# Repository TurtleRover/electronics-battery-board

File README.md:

<p align="center">
  
</p>
<h1 align="center">Electronics: Battery board</h1>
<h4 align="center">This is battery board designed for Turtle rover.</h4>  

<p align="center">

</p>
<p align="center">
  <a href="http://turtlerover.com" alt="Website">Website</a> |
  <a href="https://www.facebook.com/TurtleRover/" alt="Facebook">Facebook</a> |
  <a href="https://www.youtube.com/channel/UCxukvEct3wP0S5FACa3uelA" alt="YouTube">YouTube</a>
</p>

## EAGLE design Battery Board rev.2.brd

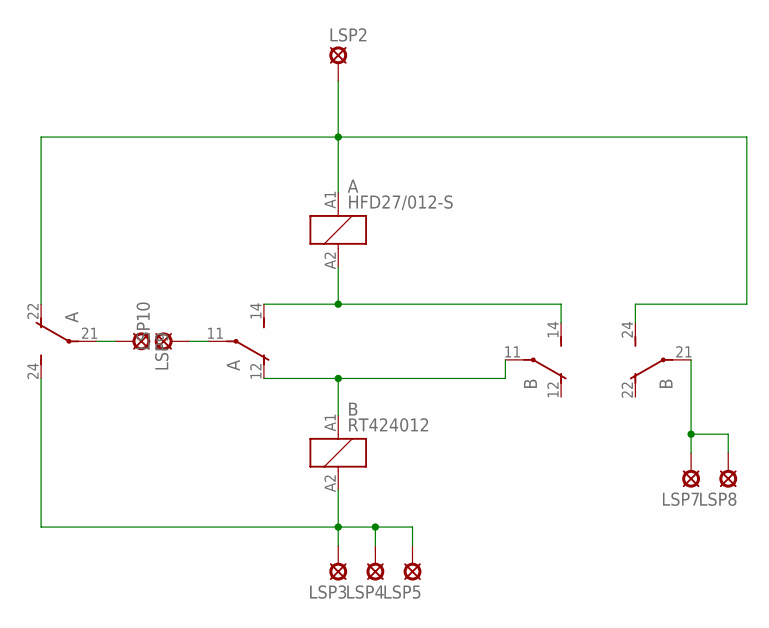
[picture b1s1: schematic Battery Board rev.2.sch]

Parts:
A: HFD27/012-S; JRC27F
B: RT424012; RT2C/O
LSP2, LSP3, LSP4, LSP5, LSP7, LSP8, LSP9, LSP10: MCS08

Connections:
BATT+: A.22 (NC), A.A1 (1), B.24 (S), LSP2.MP
BATT-: A.24 (NO), B.A2 (2), LSP3.MP, LSP4.MP, LSP5.MP
LOAD_+: B.21, LSP7.MP, LSP8.MP
unnamed: A.21 (C), LSP9.MP
unnamed: A.14 (NO), A.A2 (2), B.14 (S)
unnamed: A.12 (NC), B.11, B.A1 (1)
unnamed: A.11 (C), LSP10.MP

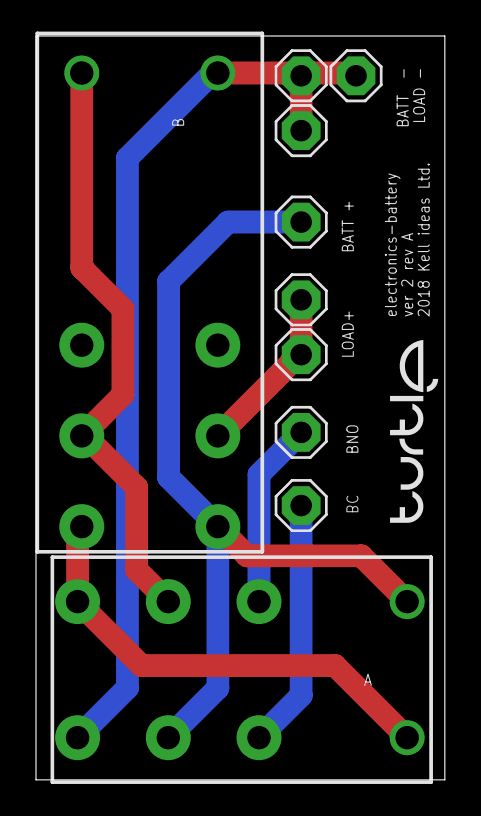
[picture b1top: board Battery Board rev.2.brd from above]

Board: 2 copper layers, 22.7 x 41.3 mm, 10 parts (0 on the bottom side), 7 nets.

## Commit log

2019-01-28 Publish on github
